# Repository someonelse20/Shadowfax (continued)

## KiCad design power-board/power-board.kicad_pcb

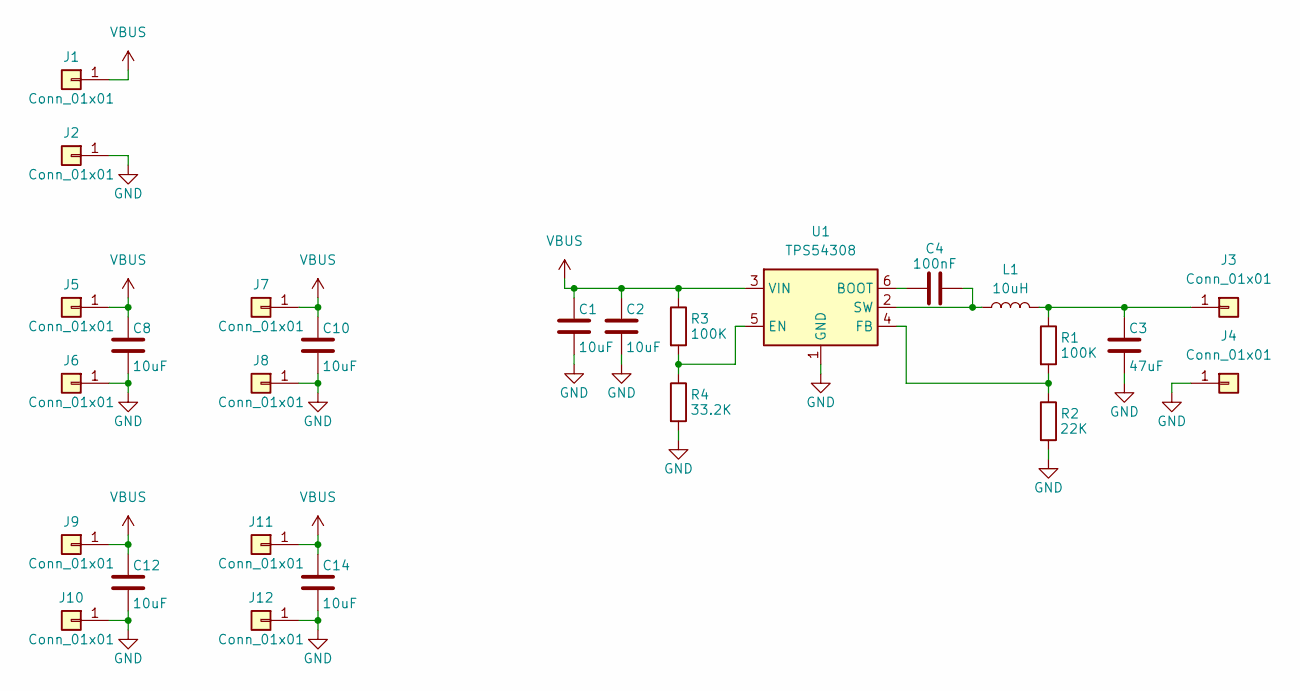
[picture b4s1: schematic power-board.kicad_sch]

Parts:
C1, C2, C8, C10, C12, C14: 10uF; C_1210_3225Metric
C3: 47uF; C_1210_3225Metric
C4: 100nF; C_0402_1005Metric
J1, J2, J3, J4, J5, J6, J7, J8, J9, J10, J11, J12: Conn_01x01; SolderWirePad_1x01_SMD_4x8mm
L1: 10uH; L_10.4x10.4_H4.8
R1, R3: 100K; R_0402_1005Metric
R2: 22K; R_0402_1005Metric
R4: 33.2K; R_0402_1005Metric
U1: TPS54308; SOT-23-6

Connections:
GND: C1.2, C2.2, C3.2, C8.2, C10.2, C12.2, C14.2, J2.1 (Pin_1_1), J4.1 (Pin_1_1), J6.1 (Pin_1_1), J8.1 (Pin_1_1), J10.1 (Pin_1_1), J12.1 (Pin_1_1), R2.2, R4.2, U1.1 (GND)
unnamed: C3.1, J3.1 (Pin_1_1), L1.2, R1.1
unnamed: C4.1, U1.6 (BOOT)
unnamed: R3.2, R4.1, U1.5 (EN)
unnamed: R1.2, R2.1, U1.4 (FB)
unnamed: C4.2, L1.1, U1.2 (SW)
VBUS: C1.1, C2.1, C8.1, C10.1, C12.1, C14.1, J1.1 (Pin_1_1), J5.1 (Pin_1_1), J7.1 (Pin_1_1), J9.1 (Pin_1_1), J11.1 (Pin_1_1), R3.1, U1.3 (VIN)

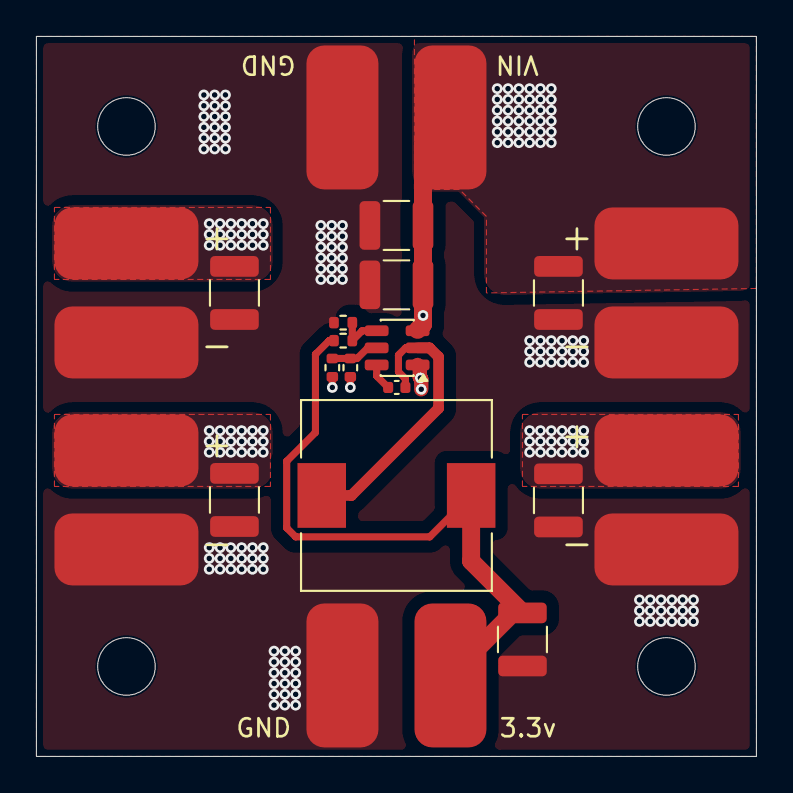
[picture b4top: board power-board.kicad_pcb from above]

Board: 4 copper layers, 40.0 x 40.0 mm, 26 parts (0 on the bottom side), 7 nets.

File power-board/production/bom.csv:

Designator,Footprint,Quantity,Value,LCSC Part #
"C1, C10, C12, C14, C2, C8",1210,6,10uF,
C3,1210,1,47uF,
C4,0402,1,100nF,
"J1, J10, J11, J12, J2, J3, J4, J5, J6, J7, J8, J9",SolderWirePad_1x01_SMD_4x8mm,12,Conn_01x01,
L1,L_10.4x10.4_H4.8,1,10uH,
"R1, R3",0402,2,100K,
R2,0402,1,22K,
R4,0402,1,33.2K,
U1,SOT-23-6,1,TPS54308,

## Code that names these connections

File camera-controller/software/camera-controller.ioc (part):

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Mcu.Name=STM32H523RCTx
Mcu.Package=LQFP64
Mcu.UserName=STM32H523RCTx
PA0.Signal=GPIO_Output
PA1.Signal=GPIO_Output
PA10.Mode=Asynchronous
PA10.Signal=USART1_RX
PA11.Mode=Device
PA11.Signal=USB_DM
PA12.Mode=Device
PA12.Signal=USB_DP
PA13(JTMS/SWDIO).Mode=Serial_Wire
PA13(JTMS/SWDIO).Signal=DEBUG_JTMS-SWDIO
PA14(JTCK/SWCLK).Mode=Serial_Wire
PA14(JTCK/SWCLK).Signal=DEBUG_JTCK-SWCLK
PA2.Signal=GPIO_Input
PA3.Signal=GPIO_Output
PA5.Mode=Full_Duplex_Master
PA5.Signal=SPI1_SCK
PA6.Mode=Full_Duplex_Master
PA6.Signal=SPI1_MISO
PA7.Mode=Full_Duplex_Master
PA7.Signal=SPI1_MOSI
PA8.Signal=GPIO_Input
PA9.Mode=Asynchronous
PA9.Signal=USART1_TX
PB0.Signal=GPIO_Input
PB1.Signal=GPIO_Input
PB12.Signal=GPIO_Input
PB13.Mode=SD_4_bits_Wide_bus
PB13.Signal=SDMMC1_D0
PB14.Signal=GPIO_Input
PB15.Signal=GPIO_Input
PB2.Mode=SD_4_bits_Wide_bus
PB2.Signal=SDMMC1_CMD
PB3(JTDO/TRACESWO).Signal=GPIO_Input
PB6.Mode=I2C
PB6.Signal=I2C1_SCL
PB7.Mode=I2C
PB7.Signal=I2C1_SDA
PC10.Mode=SD_4_bits_Wide_bus
PC10.Signal=SDMMC1_D2
PC11.Mode=SD_4_bits_Wide_bus
PC11.Signal=SDMMC1_D3
PC12.Mode=SD_4_bits_Wide_bus
PC12.Signal=SDMMC1_CK
PC14-OSC32_IN(OSC32_IN).Mode=LSE-External-Oscillator
PC14-OSC32_IN(OSC32_IN).Signal=RCC_OSC32_IN
PC15-OSC32_OUT(OSC32_OUT).Mode=LSE-External-Oscillator
PC15-OSC32_OUT(OSC32_OUT).Signal=RCC_OSC32_OUT
PC4.Signal=GPIO_Output
PC5.Signal=GPIO_Output
PC6.Signal=GPIO_Input
PC7.Signal=GPIO_Input
PC8.Signal=GPIO_Input
PC9.Mode=SD_4_bits_Wide_bus
PC9.Signal=SDMMC1_D1
PD2.Signal=GPIO_Input
PH0-OSC_IN(PH0).Mode=HSE-External-Oscillator
PH0-OSC_IN(PH0).Signal=RCC_OSC_IN
PH1-OSC_OUT(PH1).Mode=HSE-External-Oscillator
PH1-OSC_OUT(PH1).Signal=RCC_OSC_OUT
RCC.HSE_VALUE=25000000
RCC.SYSCLKFreq_VALUE=32000000
board=custom

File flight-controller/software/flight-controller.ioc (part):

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Mcu.Name=STM32H523RCTx
Mcu.Package=LQFP64
Mcu.UserName=STM32H523RCTx
PA0.Mode=Asynchronous
PA0.Signal=UART4_TX
PA1.Mode=Asynchronous
PA1.Signal=UART4_RX
PA10.Signal=GPIO_Input
PA11.Mode=Device
PA11.Signal=USB_DM
PA12.Mode=Device
PA12.Signal=USB_DP
PA13(JTMS/SWDIO).Mode=Serial_Wire
PA13(JTMS/SWDIO).Signal=DEBUG_JTMS-SWDIO
PA14(JTCK/SWCLK).Mode=Serial_Wire
PA14(JTCK/SWCLK).Signal=DEBUG_JTCK-SWCLK
PA2.Signal=GPIO_Output
PA3.Signal=GPIO_Input
PA8.Signal=S_TIM1_CH1
PA9.Signal=S_TIM1_CH2
PB1.Signal=GPIO_Input
PB12.Mode=Asynchronous
PB12.Signal=UART5_RX
PB13.Mode=Asynchronous
PB13.Signal=UART5_TX
PB14.Mode=Asynchronous
PB14.Signal=USART1_TX
PB15.Mode=Asynchronous
PB15.Signal=USART1_RX
PB2.Signal=GPIO_Input
PB4(NJTRST).Signal=S_TIM3_CH1
PB5.Signal=S_TIM3_CH2
PB6.Mode=I2C
PB6.Signal=I2C1_SCL
PB7.Mode=I2C
PB7.Signal=I2C1_SDA
PC14-OSC32_IN(OSC32_IN).Mode=LSE-External-Oscillator
PC14-OSC32_IN(OSC32_IN).Signal=RCC_OSC32_IN
PC15-OSC32_OUT(OSC32_OUT).Mode=LSE-External-Oscillator
PC15-OSC32_OUT(OSC32_OUT).Signal=RCC_OSC32_OUT
PC6.Mode=Asynchronous
PC6.Signal=USART6_TX
PC7.Mode=Asynchronous
PC7.Signal=USART6_RX
PH0-OSC_IN(PH0).Mode=HSE-External-Oscillator
PH0-OSC_IN(PH0).Signal=RCC_OSC_IN
PH1-OSC_OUT(PH1).Mode=HSE-External-Oscillator
PH1-OSC_OUT(PH1).Signal=RCC_OSC_OUT
RCC.HSE_VALUE=25000000
RCC.SYSCLKFreq_VALUE=32000000
board=custom

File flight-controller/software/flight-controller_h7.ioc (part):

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Mcu.Name=STM32H7A3R(G-I)Tx
Mcu.Package=LQFP64
Mcu.UserName=STM32H7A3RGTx
PA0.Mode=Asynchronous
PA0.Signal=UART4_TX
PA1.Mode=Asynchronous
PA1.Signal=UART4_RX
PA10.Signal=GPIO_Input
PA11.Mode=Host_FS
PA11.Signal=USB_OTG_HS_DM
PA12.Mode=Host_FS
PA12.Signal=USB_OTG_HS_DP
PA13.Mode=Serial_Wire
PA13.Signal=DEBUG_JTMS-SWDIO
PA14.Mode=Serial_Wire
PA14.Signal=DEBUG_JTCK-SWCLK
PA2.Signal=GPIO_Output
PA3.Signal=GPIO_Input
PA8.Signal=S_TIM1_CH1
PA9.Signal=S_TIM1_CH2
PB1.Signal=GPIO_Input
PB12.Mode=Asynchronous
PB12.Signal=UART5_RX
PB13.Mode=Asynchronous
PB13.Signal=UART5_TX
PB14.Mode=Asynchronous
PB14.Signal=USART1_TX
PB15.Mode=Asynchronous
PB15.Signal=USART1_RX
PB2.Signal=GPIO_Input
PB6.Signal=S_TIM4_CH1
PB7.Signal=S_TIM4_CH2
PB8.Mode=I2C
PB8.Signal=I2C1_SCL
PB9.Mode=I2C
PB9.Signal=I2C1_SDA
PC14-OSC32_IN.Mode=LSE-External-Oscillator
PC14-OSC32_IN.Signal=RCC_OSC32_IN
PC15-OSC32_OUT.Mode=LSE-External-Oscillator
PC15-OSC32_OUT.Signal=RCC_OSC32_OUT
PC6.Mode=Asynchronous
PC6.Signal=USART6_TX
PC7.Mode=Asynchronous
PC7.Signal=USART6_RX
PH0-OSC_IN.Mode=HSE-External-Oscillator
PH0-OSC_IN.Signal=RCC_OSC_IN
PH1-OSC_OUT.Mode=HSE-External-Oscillator
PH1-OSC_OUT.Signal=RCC_OSC_OUT
RCC.SYSCLKFreq_VALUE=64000000
board=custom

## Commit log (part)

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2026-04-09 init files
2026-04-11 selected esc mosfet
2026-04-13 changed flight controller mcu
2026-04-13 added ground sensor
2026-04-13 worked on camera controller schematic
2026-04-13 added micro sd card holder
2026-04-13 made camera controller schematic
2026-04-13 started pcb
2026-04-14 made camera controller pcb layout
2026-04-14 made transceiver schematic
2026-05-20 added mcu and gps
2026-05-23 changed mcu and added gps
2026-05-25 first draft of transceiver pcb
2026-05-25 touched up schematic
2026-05-31 updated board and started frame
2026-06-01 working on frame
2026-06-07 added frame feet
2026-06-08 prototyped frame
2026-06-10 updated frame feet
2026-06-15 testing pcb pannels
2026-06-25 finished camera controller pcb
2026-06-26 finished transceiver pcb
2026-06-26 fixed via issues
2026-06-26 oops forgot to save
2026-06-27 finished flight controller pcb
2026-06-27 added power board
2026-06-28 added frame top and assembly
2026-06-28 optimized power trace
2026-06-28 started production pcb
2026-06-30 outlined README.md
2026-06-30 added production files
2026-06-30 added assets
2026-06-30 cleaning up
2026-06-30 added frame image
